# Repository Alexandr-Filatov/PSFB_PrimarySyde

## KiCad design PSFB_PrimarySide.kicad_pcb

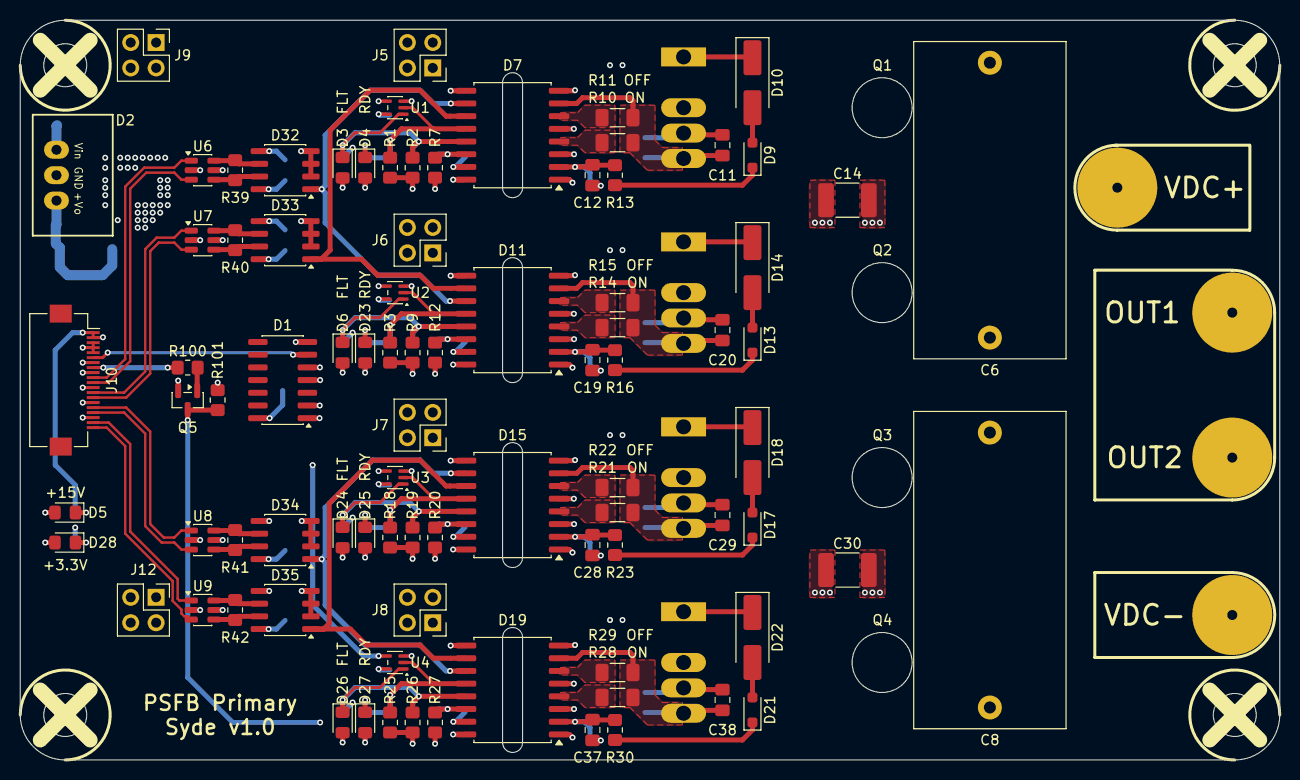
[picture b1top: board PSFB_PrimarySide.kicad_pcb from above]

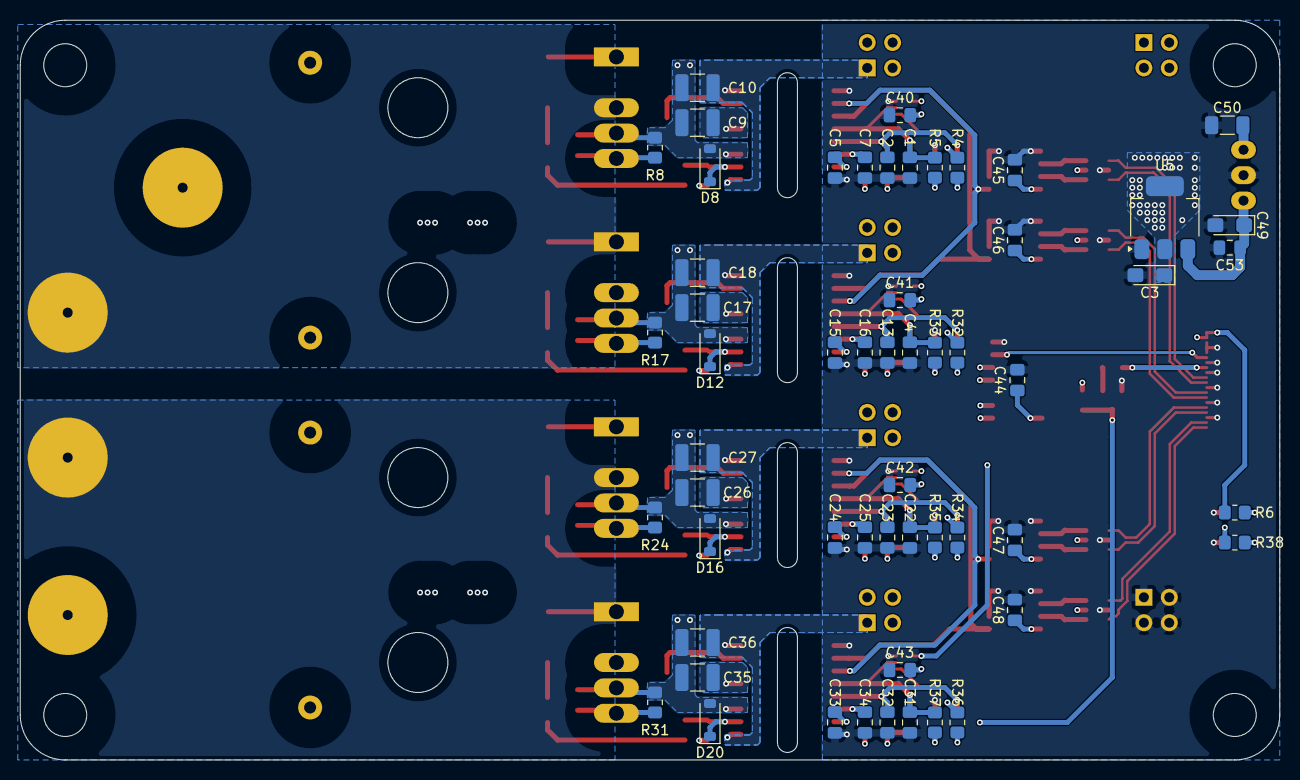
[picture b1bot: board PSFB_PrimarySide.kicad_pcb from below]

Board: 4 copper layers, 126.0 x 74.0 mm, 154 parts (56 on the bottom side), 90 nets.

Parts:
C1, C2, C4, C7, C13, C16, C22, C23, C25, C31, C32, C34: 56p; C_0805_2012Metric_Pad1.18x1.45mm_HandSolder
C3: 22u; CP_EIA-3216-18_Kemet-A_HandSolder
C5, C15, C24, C33, C40, C41, C42, C43, C44, C45, C46, C47, C48, C53: 100n; C_0805_2012Metric_Pad1.18x1.45mm_HandSolder
C6, C8: 5u; C_Rect_L31.5mm_W15.0mm_P27.50mm_MKS4
C9, C10, C17, C18, C26, C27, C35, C36: 10u; C_1210_3225Metric_Pad1.33x2.70mm_HandSolder
C11, C20, C29, C38: C_0805_2012Metric_Pad1.18x1.45mm_HandSolder
C12, C19, C28, C37: 22p; C_0805_2012Metric_Pad1.18x1.45mm_HandSolder
C14, C30: 100n; C_1812_4532Metric_Pad1.57x3.40mm_HandSolder
C49: 10u; CP_EIA-3216-18_Kemet-A_HandSolder
C50: 10u; C_1206_3216Metric_Pad1.33x1.80mm_HandSolder
D1: SOIC-14_3.9x8.7mm_P1.27mm
D2: K78xx-500R3 ÕýÊä³ö
D3, D4, D5, D6, D23, D24, D25, D26, D27, D28: LED_0805_2012Metric_Pad1.15x1.40mm_HandSolder
D7, D11, D15, D19: SOIC-16W_7.5x10.3mm_P1.27mm
D8, D12, D16, D20: D_SOD-123
D9, D13, D17, D21: D_SOD-323_HandSoldering
D10, D14, D18, D22: D_SMA_Handsoldering
D32, D33, D34, D35: SO-8_3.9x4.9mm_P1.27mm
H1, H2, H3, H4: MountingHole_4.3mm_M4
J1: DC+; Bush_1x8
J2: DC-; Bush_1x8
J3: OUT1; Bush_1x8
J4: OUT2; Bush_1x8
J5, J6, J7, J8, J9, J12: PinSocket_2x02_P2.54mm_Vertical
J10: Hirose_FH12-20S-0.5SH_1x20-1MP_P0.50mm_Horizontal
Q1, Q2, Q3, Q4: TO-247-4_Horizontal_TabDown
Q5: SOT-23
R1, R2, R3, R4, R5, R9, R18, R19, R25, R26, R32, R33, R34, R35, R36, R37, R38, R101: 1k; R_0805_2012Metric_Pad1.20x1.40mm_HandSolder
R6: 3k; R_0805_2012Metric_Pad1.20x1.40mm_HandSolder
R7, R12, R20, R27: 120; R_0805_2012Metric_Pad1.20x1.40mm_HandSolder
R8, R17, R24, R31: 10k; R_0805_2012Metric_Pad1.20x1.40mm_HandSolder
R10, R14, R21, R28: 10; R_1206_3216Metric_Pad1.30x1.75mm_HandSolder
R11, R15, R22, R29: 2.2; R_1206_3216Metric_Pad1.30x1.75mm_HandSolder
R13, R16, R23, R30, R39, R40, R41, R42: 100; R_0805_2012Metric_Pad1.20x1.40mm_HandSolder
R100: 4.7k; R_0805_2012Metric_Pad1.20x1.40mm_HandSolder
U1, U2, U3, U4: SOT-353_SC-70-5
U5: SOT-223-3_TabPin2
U6, U7, U8, U9: SOT-23-6

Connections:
+3.3V: C3.1, C5.2, C15.2, C24.2, C33.2, C40.2, C41.2, C42.2, C43.2, C44.2, C45.1, C46.1, C47.1, C48.1, D1.14 (Vcc), D7.15 (Vcc1), D11.15 (Vcc1), D15.15 (Vcc1), D19.15 (Vcc1), D32.8 (VCC), D33.8 (VCC), D34.8 (VCC), D35.8 (VCC), R1.2, R2.2, R3.2, R4.2, R9.2, R18.2, R19.2, R25.2, R26.2, R32.2, R34.2, R36.2, R38.2, R101.2, U1.5 (VCC), U2.5 (VCC), U3.5 (VCC), U4.5 (VCC), U5.2 (VO), U6.5 (VBUS), U7.5 (VBUS), U8.5 (VBUS), U9.5 (VBUS)
+15V: C50.1, D2.1 (Vin), J9.1, J9.2, J9.3, J9.4, J10.1, J10.2, R6.2
/+5V: C49.1, C53.1, D2.3 (+Vo), U5.3 (VI)
/Common_FLT1: D1.5 (1D), U1.4
/Common_FLT2: D1.4 (1C), U2.4
/Common_FLT3: D1.2 (1B), U3.4
/Common_FLT4: D1.1 (1A), U4.4
/Driver_1/+15V: C9.1, D7.5 (Vcc2), J5.2
/Driver_1/-4V: C10.2, D7.1 (Vee2), D7.8 (Vee2), J5.1
/Driver_1/GND2: C9.2, C10.1, C11.1, C12.2, D7.3 (GND2), D8.2 (A), D14.1 (K), J3.1 (Pin_1_1), J5.3, J5.4, Q1.2 (S), Q1.3 (DS), Q2.1 (D), R8.1
/Driver_1/RDY: C1.1, D7.12 (RDY), R1.1, R5.2, U1.2
/Driver_1/~FLT: C2.1, D3.1 (K), D7.13 (~FLT), R2.1, U1.1
/Driver_1/~RST: Q5.3 (C), R7.1, R12.1, R20.1, R27.1, R101.1
/Driver_2/+15V: C17.1, D11.5 (Vcc2), J6.2
/Driver_2/-4V: C18.2, D11.1 (Vee2), D11.8 (Vee2), J6.1
/Driver_2/RDY: C4.1, D11.12 (RDY), R3.1, R33.2, U2.2
/Driver_2/~FLT: C13.1, D6.1 (K), D11.13 (~FLT), R9.1, U2.1
/Driver_3/+15V: C26.1, D15.5 (Vcc2), J7.2
/Driver_3/-4V: C27.2, D15.1 (Vee2), D15.8 (Vee2), J7.1
/Driver_3/GND2: C26.2, C27.1, C28.2, C29.1, D15.3 (GND2), D16.2 (A), D22.1 (K), J4.1 (Pin_1_1), J7.3, J7.4, Q3.2 (S), Q3.3 (DS), Q4.1 (D), R24.1
/Driver_3/RDY: C22.1, D15.12 (RDY), R18.1, R35.2, U3.2
/Driver_3/~FLT: C23.1, D15.13 (~FLT), D24.1 (K), R19.1, U3.1
/Driver_4/+15V: C35.1, D19.5 (Vcc2), J8.2
/Driver_4/-4V: C36.2, D19.1 (Vee2), D19.8 (Vee2), J8.1
/Driver_4/RDY: C31.1, D19.12 (RDY), R25.1, R37.2, U4.2
/Driver_4/~FLT: C32.1, D19.13 (~FLT), D26.1 (K), R26.1, U4.1
/ERROR: D1.6 (1Y), J10.6
/PWM_H1: D7.10 (IN+), D11.11 (IN-), D32.1 (RO)
/PWM_H1_N: J10.11, U6.3 (I/O2)
/PWM_H1_P: J10.10, U6.1 (I/O1)
/PWM_H2: D15.10 (IN+), D19.11 (IN-), D34.1 (RO)
/PWM_H2_N: J10.17, U8.3 (I/O2)
/PWM_H2_P: J10.16, U8.1 (I/O1)
/PWM_L1: D7.11 (IN-), D11.10 (IN+), D33.1 (RO)
/PWM_L1_N: J10.14, U7.3 (I/O2)
/PWM_L1_P: J10.13, U7.1 (I/O1)
/PWM_L2: D15.11 (IN-), D19.10 (IN+), D35.1 (RO)
/PWM_L2_N: J10.20, U9.3 (I/O2)
/PWM_L2_P: J10.19, U9.1 (I/O1)
/RST: J10.8, R100.1
GND: C1.2, C2.2, C3.2, C4.2, C5.1, C7.1, C13.2, C15.1, C16.1, C22.2, C23.2, C24.1, C25.1, C31.2, C32.2, C33.1, C34.1, C40.1, C41.1, C42.1, C43.1, C44.1, C45.2, C46.2, C47.2, C48.2, C49.2, C50.2, C53.2, D1.7 (GND), D2.2 (GND), D4.1 (K), D5.1 (K), D7.9 (GND1), D7.16 (TEST), D11.9 (GND1), D11.16 (TEST), D15.9 (GND1), D15.16 (TEST), D19.9 (GND1), D19.16 (TEST), D23.1 (K), D25.1 (K), D27.1 (K), D28.1 (K), D32.2 (~RE), D32.3 (DE), D32.4 (DI), D32.5 (GND), D33.2 (~RE), D33.3 (DE), D33.4 (DI), D33.5 (GND), D34.2 (~RE), D34.3 (DE), D34.4 (DI), D34.5 (GND), D35.2 (~RE), D35.3 (DE), D35.4 (DI), D35.5 (GND), J10.3, J10.4, J10.5, J10.7, J10.9, J10.12, J10.15, J10.18, J12.1, J12.2, J12.3, J12.4, Q5.2 (E), U1.3 (GND), U2.3 (GND), U3.3 (GND), U4.3 (GND), U5.1 (GND), U6.2 (GND), U7.2 (GND), U8.2 (GND), U9.2 (GND)
GNDPWR: C6.2, C8.2, C14.2, C17.2, C18.1, C19.2, C20.1, C30.2, C35.2, C36.1, C37.2, C38.1, D11.3 (GND2), D12.2 (A), D19.3 (GND2), D20.2 (A), J2.1 (Pin_1_1), J6.3, J6.4, J8.3, J8.4, Q2.2 (S), Q2.3 (DS), Q4.2 (S), Q4.3 (DS), R17.1, R31.1
unnamed: D3.2 (A), R4.1
unnamed: D4.2 (A), R5.1
unnamed: D5.2 (A), R6.1
unnamed: D6.2 (A), R32.1
unnamed: C11.2, D7.7 (CLAMP), Q1.4 (G), R8.2, R10.1, R11.2
unnamed: C12.1, D7.2 (DESAT), D8.1 (K), R13.2
unnamed: D7.4 (OUTH), R10.2
unnamed: D7.6 (OUTL), R11.1
unnamed: C7.2, D7.14 (~RST), R7.2
unnamed: D9.1 (K), R13.1
unnamed: D9.2 (A), D10.2 (A)
unnamed: C20.2, D11.7 (CLAMP), Q2.4 (G), R14.1, R15.2, R17.2
unnamed: C19.1, D11.2 (DESAT), D12.1 (K), R16.2
unnamed: D11.4 (OUTH), R14.2
unnamed: D11.6 (OUTL), R15.1
unnamed: C16.2, D11.14 (~RST), R12.2
unnamed: D13.2 (A), D14.2 (A)
unnamed: D13.1 (K), R16.1
unnamed: C29.2, D15.7 (CLAMP), Q3.4 (G), R21.1, R22.2, R24.2
unnamed: C28.1, D15.2 (DESAT), D16.1 (K), R23.2
unnamed: D15.4 (OUTH), R21.2
unnamed: D15.6 (OUTL), R22.1
unnamed: C25.2, D15.14 (~RST), R20.2
unnamed: D17.2 (A), D18.2 (A)
unnamed: D17.1 (K), R23.1
unnamed: C38.2, D19.7 (CLAMP), Q4.4 (G), R28.1, R29.2, R31.2
unnamed: C37.1, D19.2 (DESAT), D20.1 (K), R30.2
unnamed: D19.4 (OUTH), R28.2
unnamed: D19.6 (OUTL), R29.1
unnamed: C34.2, D19.14 (~RST), R27.2
unnamed: D21.2 (A), D22.2 (A)
unnamed: D21.1 (K), R30.1
unnamed: D23.2 (A), R33.1
unnamed: D24.2 (A), R34.1
unnamed: D25.2 (A), R35.1
unnamed: D26.2 (A), R36.1
unnamed: D27.2 (A), R37.1
unnamed: D28.2 (A), R38.1
unnamed: D32.6 (A), R39.2, U6.6 (I/O1)
unnamed: D32.7 (B), R39.1, U6.4 (I/O2)
unnamed: D33.6 (A), R40.2, U7.6 (I/O1)
unnamed: D33.7 (B), R40.1, U7.4 (I/O2)
unnamed: D34.6 (A), R41.2, U8.6 (I/O1)
unnamed: D34.7 (B), R41.1, U8.4 (I/O2)
unnamed: D35.6 (A), R42.2, U9.6 (I/O1)
unnamed: D35.7 (B), R42.1, U9.4 (I/O2)
unnamed: Q5.1 (B), R100.2
VDC: C6.1, C8.1, C14.1, C30.1, D10.1 (K), D18.1 (K), J1.1 (Pin_1_1), Q1.1 (D), Q3.1 (D)

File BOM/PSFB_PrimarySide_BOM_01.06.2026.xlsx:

Позиционное обозначение | Номинал | Корпус | Кол-во
R10, R14, R21, R28 | 10 | SMD 1206 | 4
R13, R16, R23, R30, R39, R40, R41, R42 | 100 | SMD 0805 | 8
C5, C15, C24, C33, C40, C41, C42, C43, C44, C45, C46, C47, C48, C53 | 100n | SMD 0805 | 14
C14, C30 | 100n | SMD 1812 | 2
R8, R17, R24, R31 | 10k | SMD 0805 | 4
C49 | 10u | CP EIA-3216-18 Kemet-A | 1
C50 | 10u | SMD 1206 | 1
C9, C10, C17, C18, C26, C27, C35, C36 | 10u | SMD 1210 | 8
R7, R12, R20, R27 | 120 | SMD 0805 | 4
R1, R2, R3, R4, R5, R9, R18, R19, R25, R26, R32, R33, R34, R35, R36, R37, R38 | 1k | SMD 0805 | 17
R11, R15, R22, R29 | 2.2 | SMD 1206 | 4
C12, C19, C28, C37 | 22p | SMD 0805 | 4
C3 | 22u | CP EIA-3216-18 Kemet-A | 1
R6 | 3k | SMD 0805 | 1
C1, C2, C4, C7, C13, C16, C22, C23, C25, C31, C32, C34 | 56p | SMD 0805 | 12
C6, C8 | 5u | Rect L31.5mm W15.0mm P27.50mm MKS4 | 2
D1 | 74HC21 | SOIC-14 3.9x8.7mm P1.27mm | 1
U1, U2, U3, U4 | 74LVC1G08 | SOT-353 SC-70-5 | 4
U5 | AMS1117-3.3 | SOT-223-3 | 1
Q1, Q2, Q3, Q4 | C3M0065100K | TO-247-4 | 4
J1 | DC+ | Bush 1x8 | 1
J2 | DC- | Bush 1x8 | 1
D2 | K78xx-500R3 | K78xx-500R3 ÕýÊä³ö | 1
D32, D33, D34, D35 | MS2111 | SO-8 3.9x4.9mm P1.27mm | 4
H1, H2, H3, H4 | MountingHole | MountingHole 4.3mm M4 | 4
D7, D11, D15, D19 | NSI6651ASC-DSWR | SOIC-16W 7.5x10.3mm P1.27mm | 4
J3 | OUT1 | Bush 1x8 | 1
J4 | OUT2 | Bush 1x8 | 1
J10 | PSFB_Control | Hirose FH12-20S-0.5SH 1x20-1MP P0.50mm | 1
J5, J6, J7, J8, J9, J12 | Supply | PinSocket 2x02 P2.54mm | 6
U6, U7, U8, U9 | USBLC6-2SC6 | SOT-23-6 | 4
D10, D14, D18, D22 | ~ | SMA | 4
C11, C20, C29, C38, D3, D4, D5, D6, D23, D24, D25, D26, D27, D28 | ~ | SMD 0805 | 14
D8, D12, D16, D20 | ~ | SOD-123 | 4
D9, D13, D17, D21 | ~ | SOD-323 | 4

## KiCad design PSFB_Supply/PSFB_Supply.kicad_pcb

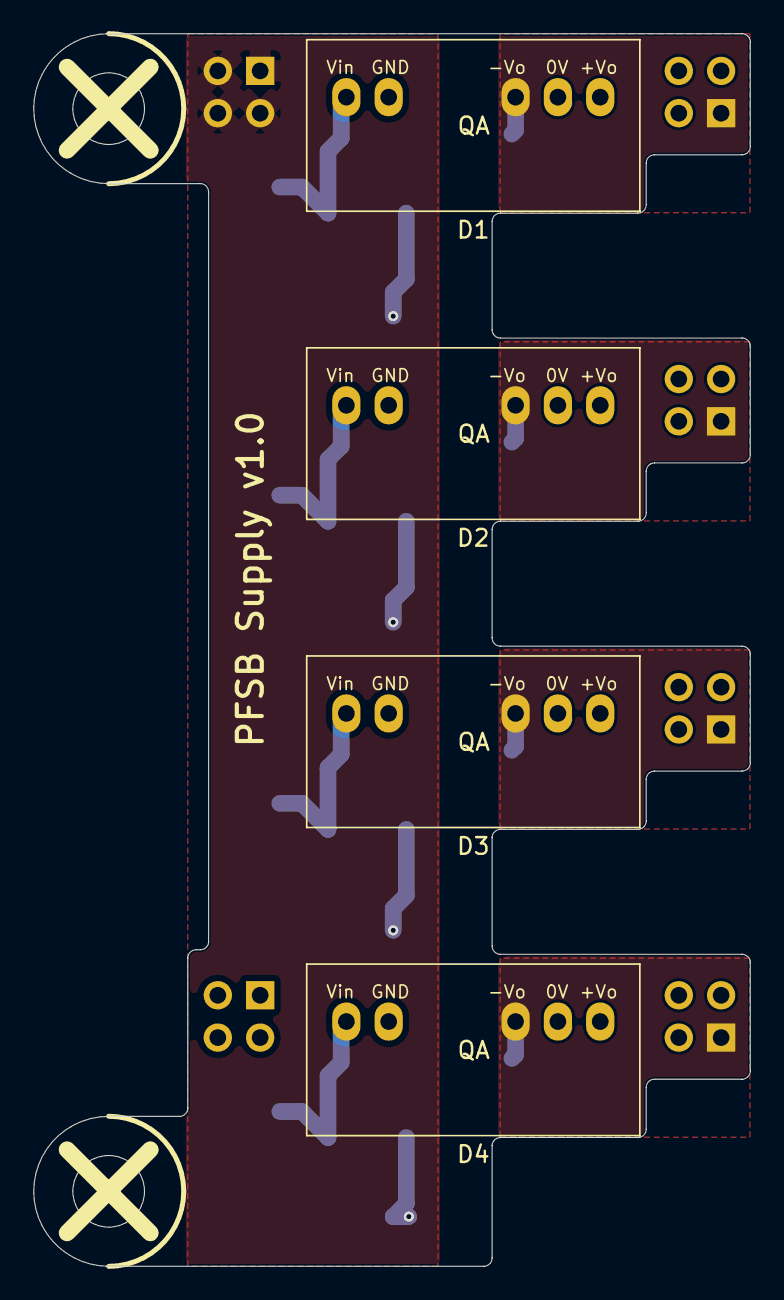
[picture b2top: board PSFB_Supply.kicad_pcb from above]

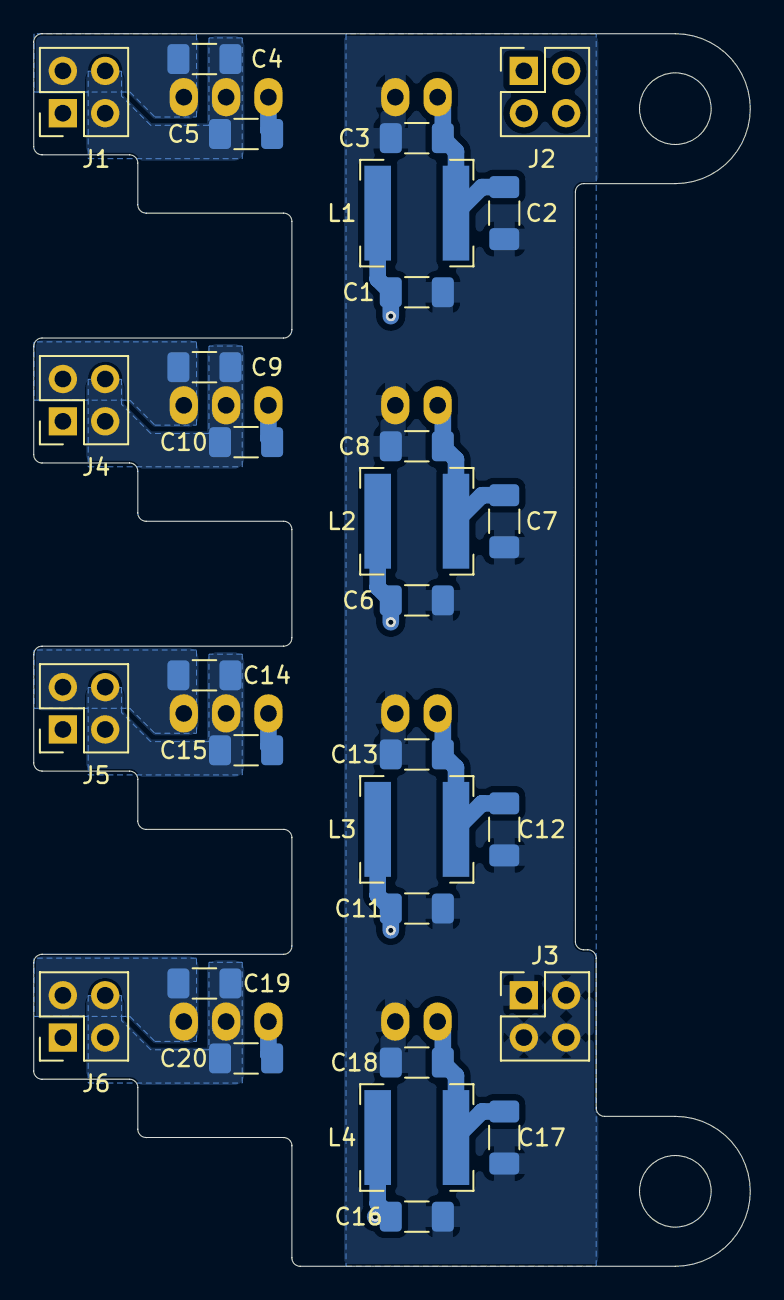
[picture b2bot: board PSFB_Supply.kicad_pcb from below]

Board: 2 copper layers, 43.0 x 74.0 mm, 36 parts (30 on the bottom side), 18 nets.

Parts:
C1, C2, C6, C7, C11, C12, C16, C17: 4.7u; C_1206_3216Metric_Pad1.33x1.80mm_HandSolder
C3, C8, C13, C18: 100p; C_1206_3216Metric_Pad1.33x1.80mm_HandSolder
C4, C5, C9, C10, C14, C15, C19, C20: 10u; C_1206_3216Metric_Pad1.33x1.80mm_HandSolder
D1, D2, D3, D4: QA01
H3, H4: MountingHole; MountingHole_4.3mm_M4
J1, J2, J3, J4, J5, J6: PinHeader_2x02_P2.54mm_Vertical
L1, L2, L3, L4: 22u; L_Bourns-SRN6028

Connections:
+15V: C1.1, C6.1, C11.1, C16.1, J2.1, J2.2, J2.3, J2.4, L1.1, L2.1, L3.1, L4.1
/QA01_1/+15V_OUT: C4.1, D1.7 (+Vo), J1.2
/QA01_1/-4V_OUT: C5.2, D1.5 (-Vo), J1.1
/QA01_1/GND2: C4.2, C5.1, D1.6 (0V), J1.3, J1.4
/QA01_2/+15V_OUT: C9.1, D2.7 (+Vo), J4.2
/QA01_2/-4V_OUT: C10.2, D2.5 (-Vo), J4.1
/QA01_2/GND2: C9.2, C10.1, D2.6 (0V), J4.3, J4.4
/QA01_3/+15V_OUT: C14.1, D3.7 (+Vo), J5.2
/QA01_3/-4V_OUT: C15.2, D3.5 (-Vo), J5.1
/QA01_3/GND2: C14.2, C15.1, D3.6 (0V), J5.3, J5.4
/QA01_4/+15V_OUT: C19.1, D4.7 (+Vo), J6.2
/QA01_4/-4V_OUT: C20.2, D4.5 (-Vo), J6.1
/QA01_4/GND2: C19.2, C20.1, D4.6 (0V), J6.3, J6.4
GND: C1.2, C2.2, C3.2, C6.2, C7.2, C8.2, C11.2, C12.2, C13.2, C16.2, C17.2, C18.2, D1.2 (GND), D2.2 (GND), D3.2 (GND), D4.2 (GND), J3.1, J3.2, J3.3, J3.4
unnamed: C2.1, C3.1, D1.1 (Vin), L1.2
unnamed: C7.1, C8.1, D2.1 (Vin), L2.2
unnamed: C12.1, C13.1, D3.1 (Vin), L3.2
unnamed: C17.1, C18.1, D4.1 (Vin), L4.2

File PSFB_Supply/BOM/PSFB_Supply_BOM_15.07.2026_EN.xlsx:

Reference | Value | Product Name | Replacement | Package | Description | Quantity | DNP
C3, C8, C13, C18 | 100p |  |  | SMD 1206 | Capacitor SMD 50V | 4
C4, C5, C9, C10, C14, C15, C19, C20 | 10u |  |  | SMD 1206 | Capacitor SMD 50V | 8
C1, C2, C6, C7, C11, C12, C16, C17 | 4.7u |  |  | SMD 1206 | Capacitor SMD 50V | 8
D1, D2, D3, D4 | ~ | QA151C3 |  | QA01 | DC/DC | 4
J1, J2, J3, J4, J5, J6 | ~ | KLS1-207-2-04-S |  | PinHeader 2x02 P2.54mm | Connector | 6
L1, L2, L3, L4 | 22u | CDRH5D28NP-220NC |  | Bourns-SRN6028 | Inductor SMD | 4

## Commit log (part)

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2026-05-25 zero commit
2026-05-25 VER1.0: убрал источники с платы
2026-05-25 VER1.0: добавил разъемы питания
2026-05-26 VER1.0: развел 4 канала
2026-05-27 VER1.0: добавил разъем под FFC
2026-05-29 VER1.0: добавил плату питания драйверов и развел всю силовую плату
2026-06-02 VER1.0: добавил ресет общий
2026-06-08 VER1.0: сделал файлы для производства
